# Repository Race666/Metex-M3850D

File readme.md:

#  Metex / Voltcraft Projects

## Project 1: A simple powershell library to read values from the multimeter

Usage of the library:
Source the library
```powershell
. .\libmetex.ps1
```
Create a new instance
```powershell
$Metex=new-object MetexM3850D("COM5")
```
Open the COM Port 
```powershell
$Metex.Open()
```
Read Measures
```powershell
$Metex.ReadMeasureSynchron()
$MeasureResult=$Metex.ReadMeasureSynchron()
```
Output should be something like this
```
MeasuringUnit    : Diode
Value            : 0
RawMeasureString : DI    OL   mV
Result           : Overload
Unit             : V
RawValue         : OL
RawUnit          : mV

MeasuringUnit    : Capacity
Value            : 4E-12
RawMeasureString : CA  0.004  nF
Result           : OK
Unit             : F
RawValue         : 0.004
RawUnit          : nF

MeasuringUnit    : CurrentDC
Value            : -1E-07
RawMeasureString : DC -000.1  uA
Result           : OK
Unit             : A
RawValue         : -000.1
RawUnit          : uA
```
Close the COM Port 
```powershell
$Metex.Close()
```

## Project 2: An adapter to connect a multimeter by a UART to USB Converter (CB2102) to a PC
The Kicad project is a simple converte to connect a M3850D by a TTL UART to USB Converter to PC.

The Description of the Serial port pins of the Multimeter:
 
RxD and TxD Ports are MAX232 compatible. Means -12V = High and +12V is Low Level. 

Therefore the ports must be inverted (done by Transistor Q1) to deal with a TTL USB adapter. This is only necessary for RxD because to start a measurement read, only a falling rise at TxD port is requiered, indepentend which character is send to the multimeter.

The multimeter serial port is isolated by optocouplers from the multimeter. A supply voltage is needed. 

DTR and RTS Ports are just used for the power supply of the optocouplers not for a serial handshake.

In my test a 5V supply is sufficent. RTS=GND DTR=5V

This is the schmetic:

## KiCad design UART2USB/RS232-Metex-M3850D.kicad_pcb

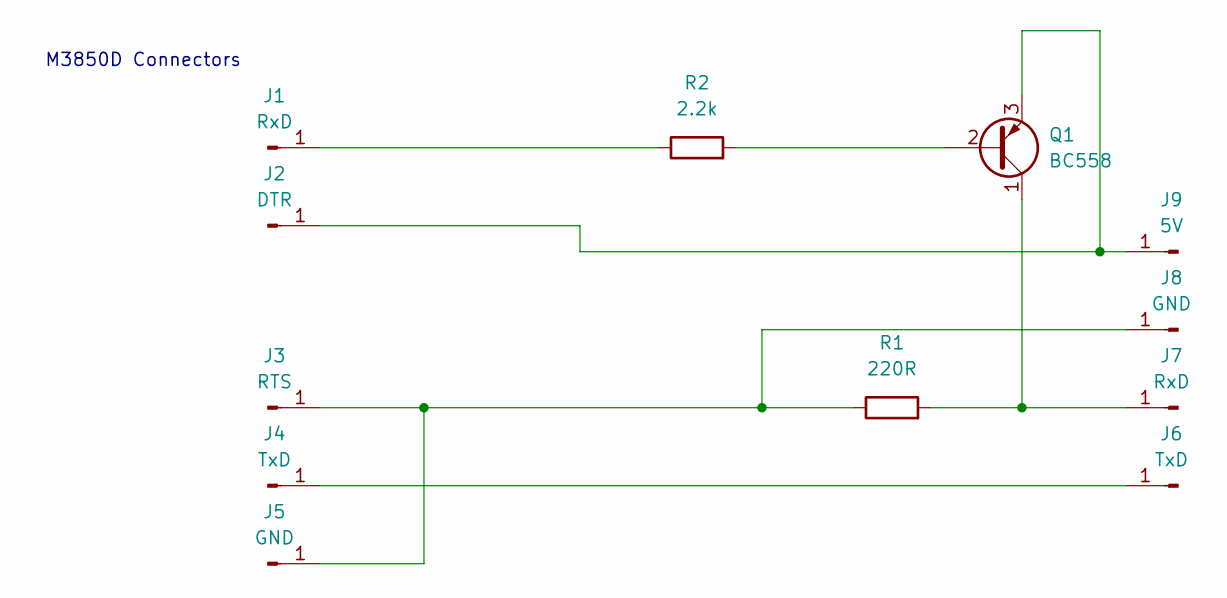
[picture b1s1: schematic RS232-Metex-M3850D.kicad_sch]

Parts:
J1, J7: RxD; PinHeader_1x01_P2.54mm_Horizontal
J2: DTR; PinHeader_1x01_P2.54mm_Horizontal
J3: RTS; PinHeader_1x01_P2.54mm_Horizontal
J4, J6: TxD; PinHeader_1x01_P2.54mm_Horizontal
J5, J8: GND; PinHeader_1x01_P2.54mm_Horizontal
J9: 5V; PinHeader_1x01_P2.54mm_Horizontal
Q1: BC558; TO-92_Inline
R1: 220R; R_Axial_DIN0207_L6.3mm_D2.5mm_P10.16mm_Horizontal
R2: 2.2k; R_Axial_DIN0207_L6.3mm_D2.5mm_P10.16mm_Horizontal

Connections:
unnamed: J1.1, R2.1
unnamed: J2.1, J9.1, Q1.3 (E)
unnamed: J3.1, J5.1, J8.1, R1.1
unnamed: J4.1, J6.1
unnamed: J7.1, Q1.1 (C), R1.2
unnamed: Q1.2 (B), R2.2

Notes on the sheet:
M3850D Connectors

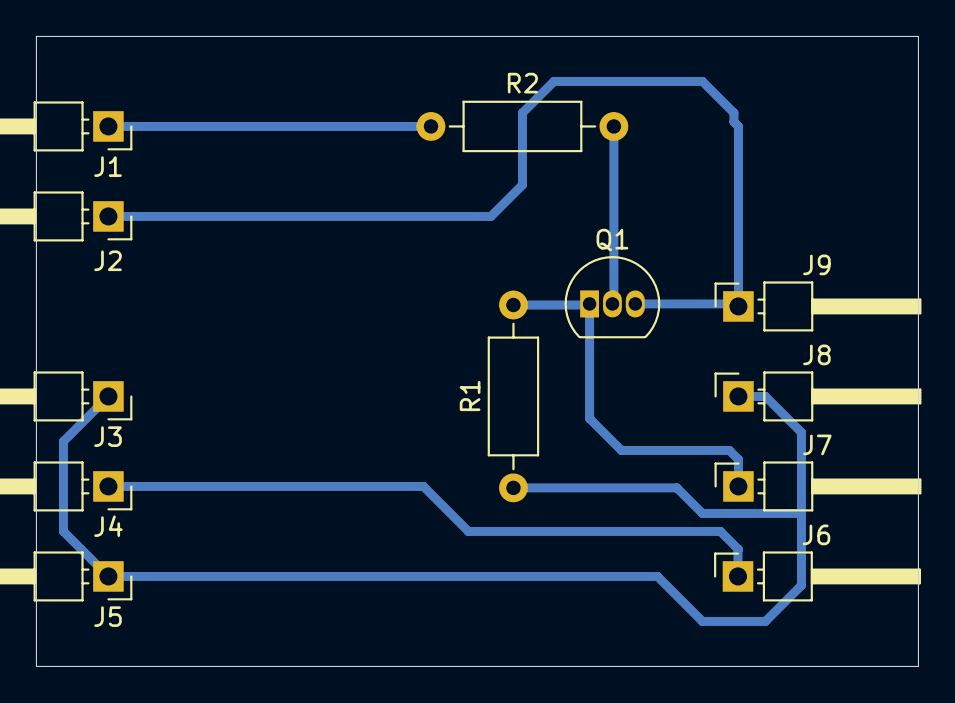
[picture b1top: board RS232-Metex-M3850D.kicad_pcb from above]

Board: 2 copper layers, 49.0 x 35.0 mm, 12 parts (0 on the bottom side), 6 nets.

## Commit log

2024-11-08 Initial release
2024-11-08 Typo fixed
2024-11-18 Some fixes
